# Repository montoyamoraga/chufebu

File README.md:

# chufebu

## About

chufebu is an open source hardware Eurorack power bus board by [piruetas](https://piruetas.xyz). It distributes ±12V, +5V, CV and GATE to five 16-pin Eurorack power headers, each one paired with its own 4-pin Molex KK-396 connector for testing. The design is made in KiCad 10 using only KiCad's standard libraries. Hardware is licensed under CERN-OHL-P-2.0 and documentation under CC-BY-SA-4.0 (see [LICENSE.md](./LICENSE.md)). Documentation, schematic, board render and bill of materials (in Spanish): <https://piruetas.xyz/chufebu/>.

## Acerca de

Bus de alimentación eurorack de [piruetas](https://piruetas.xyz), hecho en KiCad y publicado como hardware de código abierto.

Documentación, esquemático, placa y Bill of materials: <https://piruetas.xyz/chufebu/>.

## Características

- 5 headers de alimentación Eurorack de 16 pines (2x08), conectados en bus.
- Cada header tiene su conector Molex KK-396 de 4 pines, para pruebas: -12V, GND, +5V y +12V.
- Las líneas CV y GATE también van en bus entre los 5 headers.
- Placa de 100 × 45 mm, 2 capas, con 2 agujeros de montaje M3.
- Solamente usa las bibliotecas estándar de KiCad 10: no hace falta instalar bibliotecas adicionales para abrir o modificar el diseño.

## Pines y manual de uso

Los pines de los headers de 16 pines y de los conectores KK-396, cómo conectar chufebu y las advertencias están en el [manual de uso](https://piruetas.xyz/chufebu/#manual-de-uso).

## Revisiones

- `v0.1 rev-a`: fabricada en octubre 2026, todavía sin probar.

## Estructura del repositorio

- [hardware/chufebu-v-0-rev-a](./hardware/chufebu-v-0-rev-a): proyecto de KiCad (esquemático y placa), los archivos fuente del diseño.
- [hardware/chufebu-v-0-rev-a-fab](./hardware/chufebu-v-0-rev-a-fab): gerbers y archivos de taladrado para fabricar la placa.
- [docs](./docs): documentación, publicada en <https://piruetas.xyz/chufebu/>. Las capturas del esquemático y de la placa, y la tabla de Bill of materials, las genera [kicad-retrata](https://github.com/piruetasxyz/kicad-retrata) en cada push (ver [kicad-retrata.yml](./kicad-retrata.yml)).
- [LICENSES](./LICENSES): textos completos de las licencias.

## Fabricación

piruetas vende chufebu armado y probado.

Como es hardware de código abierto, los archivos fuente de KiCad, los archivos de fabricación de [hardware/chufebu-v-0-rev-a-fab](./hardware/chufebu-v-0-rev-a-fab) y la [Bill of materials](https://piruetas.xyz/chufebu/#bill-of-materials-v01-rev-a) están publicados para que cualquiera pueda estudiar, modificar y fabricar el diseño. piruetas no da soporte para unidades fabricadas o armadas por terceros.

## Créditos

- Aarón Montoya-Moraga: investigación, esquemático, PCB, fabricación y documentación.
- Matías Serrano: revisor experto de esquemáticos y PCBs.

## Licencia

chufebu es (c) 2026 piruetas SpA / Aarón Montoya-Moraga.

- Hardware (`hardware/`): [CERN-OHL-P-2.0](./LICENSES/CERN-OHL-P-2.0.txt).
- Documentación (`docs/`): [CC-BY-SA-4.0](./LICENSES/CC-BY-SA-4.0.txt).
- El nombre, logo y marca de piruetas no están cubiertos por estas licencias: ver [LicenseRef-piruetas-branding](./LICENSES/LicenseRef-piruetas-branding.txt).

Ver [LICENSE.md](./LICENSE.md) para los detalles. El repositorio sigue la especificación [REUSE](https://reuse.software/).

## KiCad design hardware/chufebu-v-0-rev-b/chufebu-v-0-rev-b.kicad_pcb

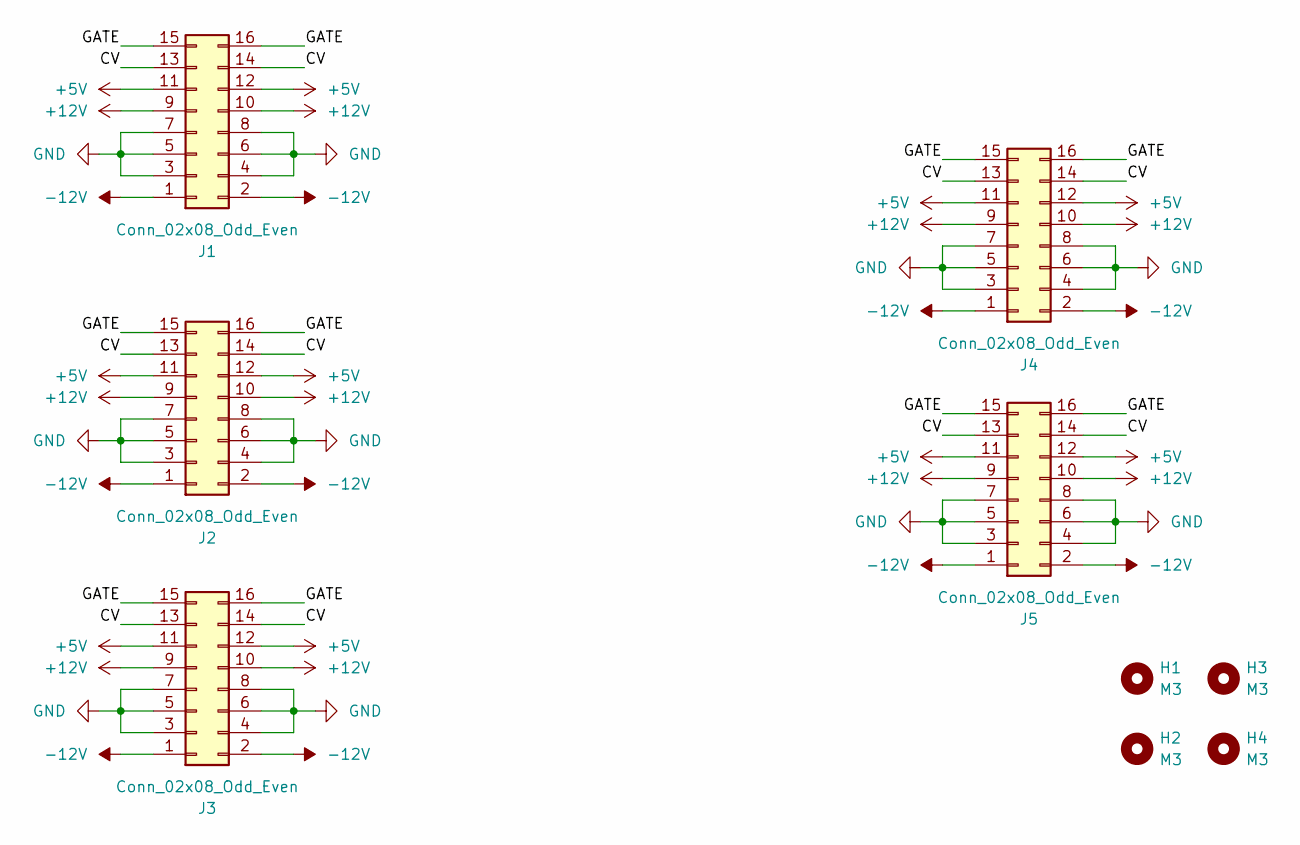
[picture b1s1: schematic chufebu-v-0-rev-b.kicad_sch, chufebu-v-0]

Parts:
H1, H2, H3, H4: M3; MountingHole_3.2mm_M3
J1, J2, J3, J4, J5: Conn_02x08_Odd_Even; IDC-Header_2x08_P2.54mm_Vertical

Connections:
+5V: J1.11, J1.12, J2.11, J2.12, J3.11, J3.12, J4.11, J4.12, J5.11, J5.12
+12V: J1.9, J1.10, J2.9, J2.10, J3.9, J3.10, J4.9, J4.10, J5.9, J5.10
-12V: J1.1, J1.2, J2.1, J2.2, J3.1, J3.2, J4.1, J4.2, J5.1, J5.2
/CV: J1.13, J1.14, J2.13, J2.14, J3.13, J3.14, J4.13, J4.14, J5.13, J5.14
/GATE: J1.15, J1.16, J2.15, J2.16, J3.15, J3.16, J4.15, J4.16, J5.15, J5.16
GND: J1.3, J1.4, J1.5, J1.6, J1.7, J1.8, J2.3, J2.4, J2.5, J2.6, J2.7, J2.8, J3.3, J3.4, J3.5, J3.6, J3.7, J3.8, J4.3, J4.4, J4.5, J4.6, J4.7, J4.8, J5.3, J5.4, J5.5, J5.6, J5.7, J5.8

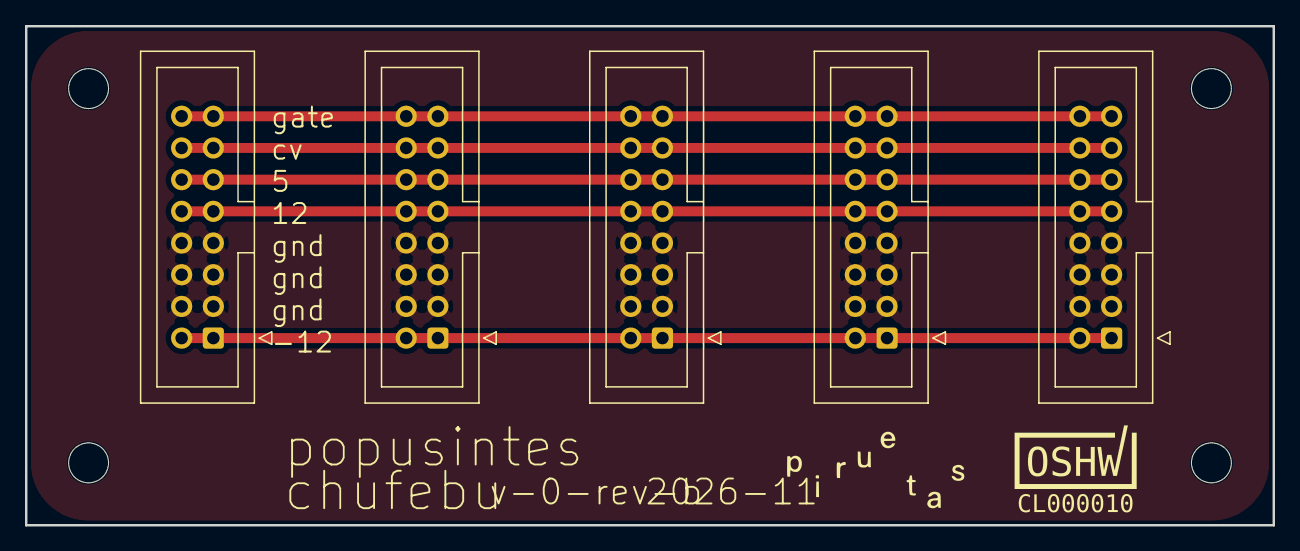
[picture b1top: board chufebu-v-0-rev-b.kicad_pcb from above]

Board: 2 copper layers, 100.0 x 40.0 mm, 9 parts (0 on the bottom side), 6 nets.
